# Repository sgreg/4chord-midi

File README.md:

# 4chord MIDI - The Four Chord USB MIDI Keyboard

What does it take to create a hit pop song?

Australia's former comedy group [The Axis of Awesome](https://en.wikipedia.org/wiki/The_Axis_of_Awesome) had the answer: [Four chords](https://www.youtube.com/watch?v=5pidokakU4I). Though not just any four chords, but the [I-V-vi-IV chord progression](https://en.wikipedia.org/wiki/I%E2%80%93V%E2%80%93vi%E2%80%93IV_progression) to be precise. This project implements a USB MIDI device for the purpose of playing this exact four-chord progression.

4chord MIDI is a regular USB MIDI controller, just like any other MIDI keyboard, except it has just four buttons, one for each chord in the I-V-vi-IV chord progression, playable in any key. But since simply playing chords is a bit limiting, it also features different playback modes such as triad arpeggios and chords mixed with arpeggios. Additionally, the tempo of each note progression is selectable from 30bpm to 240bpm. It's even shaped like a piano, to give the real feel of playing an actual musical instrument.

For additional information, check out [the 4chord MIDI project website](https://4chord.craplab.fi) and [its hackaday.io project page](https://hackaday.io/project/26078-4chord-midi).

4chord MIDI is fully open source and certified as such by the [Open Source Hardware Association (OSHWA)](https://www.oshwa.org/). The hardware is licensed under the [CERN Open Hardware License v.1.2](http://www.ohwr.org/projects/cernohl/wiki) and the software is released under the [GNU General Public License version 2](http://www.gnu.org/licenses/old-licenses/gpl-2.0.en.html).

<p align="center">

</p>

## Table of Contents
  * [Quick Start](#quick-start)
  * [Project Structure](#project-structure)
  * [Build it](#build-it)
  * [Flash it](#flash-it)
  * [Use it](#use-it)
  * [User Interface](#user-interface)
  * [Troubleshooting](#troubleshooting)

## Quick Start

If you're not interested in the details, here's the quickest way to build and flash a 4chord MIDI device. Note that the Makefile is set up to expect USBasp as programmer. If you're using a different programmer, check the [flashing section](#flash-it) for more details.

### Dependencies
Make sure you have the dependencies to build the bootloader and firmware installed on your system.

For Ubuntu, Debian, and the likes, this should be:
```
$ sudo apt install gcc-avr avr-libc avr-binutils avrdude make
```
For Fedora etc. it should be:
```
$ sudo dnf install avr-gcc avr-libc avr-binutils avrdude make
```
For Arch it should be ~~FUCKING OBVIOUS AND YOU'RE NOT WORTHY TO USE THIS GLORIOUS DISTRO IF YOU HAVE TO ASK A LAME QUESTION LIKE THIS~~ the same package names as for Fedora:
```
$ sudo pacman -S avr-gcc avr-libc avr-binutils avrdude make
```

Unfortunately, I don't have the answer for any other distribution, MacOS, or Windows, but essentially, it's just the regular AVR toolchain components (and `make`), so checking a general setup guide for the AVR toolchain on that system should get you there. Presumably it follows the same package names as mentioned so far.

### Cloning, Building, Flashing

Clone the repository and change into it:
```
$ git clone https://github.com/sgreg/4chord-midi.git
$ cd 4chord-midi/
```

Build the bootloader and firmware:
```
$ make
```

Make sure the ATmega's fuses are set up properly:
```
$ make fuses
```

Flash it to the device:
```
$ make program
```

That's it, your 4chord MIDI device should be ready to go, and once plugged in, recognized as as such. Check the [usage section](#use-it) for a quick overview of how to connect it to *FluidSynth* to get your first chords played.

If you *are* interested in more details, well here they come.

## Project Structure

* [`bootloader/`](bootloader/) the bootloader for comfortable firmware update flashing
* [`doc/`](doc/) some relevant documentation such as USB specifications
* [`firmware/`](firmware/) the main 4chord MIDI firmware code
* [`graphics/`](graphics/) raw [XBM](https://en.wikipedia.org/wiki/X_BitMap) files used within the GUI and intro animation
* [`hardware/`](hardware/) schematic and PCB design files
* [`sys/`](sys/) Linux system scripts (udev rules and setup scripts)
* [`tools/`](tools/) additional tools to convert graphics and dump fuse settings
* [`Makefile`](Makefile) main entry point to built it all
* [`common.mk`](common.mk) shared data related to building
* everything else: this README and git stuff

## Build it

From firmware point of view, there are three main parts to build here:
1. the raw XBM graphics converted to easily dump to the Nokia LCD (shipped pre-built)
1. the bootloader for future firmware updates via USB (optional but recommended)
1. the actual firmware

### Graphics
As the graphics parts come pre-built ([`intro.c`](firmware/intro.c)/[`intro.h`](firmware/intro.h) for the intro animation, [`gfx.c`](firmware/gfx.c)/[`gfx.h`](firmware/gfx.h) for all GUI related graphic elements), there's nothing to do, unless you want to change the [`graphics/`](graphics/) content by either adding new XBM files, or modifying the existing ones. In that case, once the graphics are modified, run:
```
$ make graphics
```
from the project's root path, which will delete all previously generated files and re-create them.

### Bootloader

You can build and flash the bootloader on its own without the main 4chord MIDI firmware. If this is your first time with the code, you might want to skip this option and go straight to the [Bootloader with Firmware](#bootloader-with-firmware) section for now.

But let's say you want to play around with just the bootloader and flash the application firmware through USB later, or make modifications to the bootloader itself. In that case, the bootloader can be built from the project's root directory via
```
$ make bootloader
```

or from within the `bootloader/device/` directory via `make` on its own.

This will create the bootloader's ELF and HEX file in the `bootloader/device/` directory, ready to be flashed to the device. Instructions on flashing [follow below](#flash-it).

**Note that this will build only the bootloader but not the firmware, so the device won't act as USB MIDI controller afterwards!**

Also note that once [flashed](#flash-it), the bootloader needs to be manually activated by pressing the *Select* button when powering the device up, otherwise it will fall through to the application code - which in this case won't exist. As a result, the device is stuck in a boot loop until the *Select* key is pressed. In other words, if the device seems dead after flashing the bootloader, just press the *Select* button to start up the actual bootloader.

### Firmware

As with the bootloader mentioned above, the firmware can be built and flashed on its own without adding the bootloader to it. This makes sense if you make any changes to the firmware code without touching the bootloader, but keep in mind that [flashing](#flash-it) the firmware on its own will leave out the bootloader, so future firmware updates via USB won't be possible (but you can always just re-flash the device with both components, so there's no harm done).

To build the firmware on its own from the project root directory, simply call

```
$ make firmware
```

To build it straight from within the `firmware/` directory, simply run `make` in there.

This will again create the ELF and HEX file inside the `firmware/` directory, and in addition, a BIN file. The HEX file is used for [flashing](#flash-it), while the BIN file is used in the firmware upgrade via USB using the bootloader.

### Bootloader with Firmware

To get the full package of bootloader and firmware, simply call
```
$ make
```
from within the project's root directory.

This will build both components separately, and the resulting ELF, HEX, and in case of the firmware, BIN file will be afterwards located in `bootloader/device/` and `firmware/` respectively.

You should now have either one of them built and ready to be flashed to the device.

## Flash it

If you're building your own device, you will require an AVR programmer to flash the initial bootloader and/or firmware to it. If you got a ready-made device, it will come with an initial bootloader and firmware already flashed on it, in which case you can either still use an AVR programmer to update it, or use the bootloader's built-in update functionality.

### Flashing with an AVR Programmer

The build system is set up to expect USBasp as programmer, so if you're using a different programmer, flashing is of course going to fail. To set up the build system for your programmer, check the [`common.mk`](common.mk) file for the following line:

```
AVRDUDE_PROGRAMMER_FLAGS = -c usbasp
```
and adjust it to your needs. If the programmer requires an additional port parameter, add the `-P <port>` accordingly.

Note that the device uses a 6-pin ISP connector, although some programmers - including a regular USBasp programmer - comes with a 10-pin connector. The 10-pin version has in the end just 4 additional, unused pins, which seems unnecessary, so the choice was to go for the 6-pin version here. The connectors are otherwise compatible, it just needs either an adapter or manual wiring.

To make sure the programmer is set up properly, connect it to the 4chord MIDI device and run
```
$ make check-programmer
```
from within the project's root directory. If both the programmer and device was detected, you should `SUCCESS` displayed in the end. Note that if you didn't connect the 4chord MIDI device, you might still see `FAILURE` even though the programmer is set up correctly. `avrdude`'s error message should hopefully give some hints which part went wrong then.

If everything is happily set up, connect the programmer to the device and get ready to flash.

Depending on the parts you [built earlier](#build-it), you can either flash the bootloader and firmware on its own, or nicely combined for the full experience.

For the latter, run the following command from the project's root directory:
```
$ make program
```
To flash only the bootloader, which won't include the firmware itself and therefore won't turn the device into an actual MIDI controller, run the command from within the bootloader directory:
```
$ cd bootloader/device/
$ make program
```
To flash only the firmware without the bootloader, flash it from the firmware's directory accordingly:
```
$ cd firmware/
$ make program
```

In case you included the firmware in your flashing, you're ready to [use it](#use-it). If you only flashed the bootloader and want to add the firmware through it, keep reading.

### Flashing via Bootloader

Whether the device runs *only* the bootloader, or the whole package, as long as there's a bootloader, you can use it to flash the actual 4chord MIDI firmware on it.

Flashing the firmware via bootloader involves two parts:
1. the activated bootloader on the device
2. the host-side flashing tool

To activate the bootloader, press the *Select* button while you power up the device, i.e. keep the *Select* button pressed when you plug in the USB cable to either your computer or the device itself. Instead of the 4chord MIDI startup animation and its user interface, you'll be greeted by the bootflash screen, telling you to feed it firmware.

The [host-side flashing tool](bootloader/host/) is a Python script using [PyUSB](https://github.com/pyusb/pyusb) to communicate with the bootloader - so make sure you have both Python 3 and the PyUSB module installed, whether through `pip` or your Linux distro's package manager.

With the device set up to receive new firmware, change into the host-side flashing tool's directory and run the script, giving the path of the new firmware's BIN file. If you built the firmware from its regular location, it will look like this:
```
$ cd bootloader/host/
$ ./bootflash.py ../../firmware/4chordmidi.bin
```

As you run the script, you will see some information and progress status displayed on the command line, and the device will show a progress bar on its screen. Once everything is done, you're ready to boot into the new firmware.

You can either just unplug the cable and plug it back in (making sure not to press the *Select* button this time), or press the *I* and *IV* playback button (i.e. the left-most and right-most white buttons).

## Use it

This section exclusive covers using the device under Linux, but since 4chord MIDI implements standard USB and MIDI specifications, other operating systems should treat it just like any other MIDI device. The general instructions of using MIDI devices on other operating systems should therefore apply also to 4chord MIDI.

### Plug it in

Connect 4chord MIDI to your computer and check if it got recognized. `dmesg` or the system log should show something like this:
```
[3038097.883853] usb 1-1.1.1: new low-speed USB device number 112 using ehci-pci
[3038099.140623] usb 1-1.1.1: New USB device found, idVendor=1209, idProduct=deaf
[3038099.140626] usb 1-1.1.1: New USB device strings: Mfr=1, Product=2, SerialNumber=0
[3038099.140627] usb 1-1.1.1: Product: 4chord MIDI
[3038099.140628] usb 1-1.1.1: Manufacturer: CrapLab
```

And thanks to [pid.codes](http://pid.codes/), `lsusb` should show something like this:
```
Bus 001 Device 112: ID 1209:deaf Generic CrapLab 4chord MIDI
```
Of course, the bus and device number will most certainly differ, but as long as the VID/PID pair (`1209:deaf`) is the same, it's all good.

### Simple playback with FluidSynth

As 4chord MIDI is just the controller in the MIDI chain, you will need a synthesizer to turn the playback into actual music. A cross-platform choice for this is for example the [FluidSynth software synthesizer](https://en.wikipedia.org/wiki/FluidSynth) in combination with its related sound font files.

FluidSynth can use different audio driver, including ALSA, PulseAudio, and [jack](https://en.wikipedia.org/wiki/JACK_Audio_Connection_Kit). To make life easy, let's use ALSA for this example.

#### Dependencies
Here's how to install ALSA utilities, FluidSynth with the sound fonts, and the resulting path of the sound font file we'll need afterwards.

Ubuntu / Debian / etc:
```
$ sudo apt install fluidsyinth fluid-soundfont-gm alsa-utils
/usr/share/sounds/sf2/FluidR3_GM.sf2
```
Note that the soundfont might also be named `fluidsynth-soundfont-gm` in older versions

Fedora etc:
```
$ sudo dnf install fluidsynth fluid-soundfont-gm alsa-utils
/usr/share/soundfonts/FluidR3_GM.sf2
```
Arch:
```
$ sudo pacman -S fluidsynth soundfont-fluid alsa-utils
/usr/share/soundfonts/FluidR3_GM.sf2
```

Again, for other distributions and operating systems, check the internet.

#### Running FluidSynth

Open up a terminal and start FluidSynth:

```
$ fluidsynth -a alsa -m alsa_seq /usr/share/soundfonts/FluidR3_GM.sf2
```

Make sure to use the correct sound font path according to your distro / operating system.

Once FluidSynth is started, and a 4chord MIDI device is connected to your computer, we need to connect the two using `aconnect` from the ALSA utils. Open up another terminal and check the input and output port IDs of the two parties involved.

```
$ aconnect -i
client 20: '4chord MIDI' [type=kernel]
    0 '4chord MIDI MIDI 1'

$ aconnect -o
client 129: 'FLUID Synth (32590)' [type=user]
    0 'Synth input port (32590:0)'
```

Your output probably shows more devices in each command, but those are the ones to look for. It tells us that 4chord MIDI is input port `20:0` and FluidSynth as MIDI output is port `129:0`. All that's left to do is connect the two:

```
$ aconnect 20:0 129:0
```

That's it. If you press any of the white playback buttons, you should hear a piano sound of the chords. Congratulations!

#### Changing instruments

If you want a change from the default Yamaha Grand Piano, go back to the terminal that runs FluidSynth and check the list of available instruments within its own command line. Since there's only one sound font file, its ID is simply `1`.
```
> inst 1
000-000 Yamaha Grand Piano
000-001 Bright Yamaha Grand
000-002 Electric Piano
...
000-025 Steel String Guitar
...
>
```

Changing the playback instrument for example to the Steel String Guitar (instrument id 25) for the default MIDI channel 0 is done via the `prog <chan> <instrument>` command:
```
> prog 0 25
```

You should now hear a guitar sound from the 4chord MIDI device.

### Automatic FluidSynth Setup

If you want to start FluidSynth automatically when you connect a 4chord MIDI device to you computer, you can do so on Linux with a udev rule. Check the [`sys/udev/`](sys/udev/) directory for further information on that.

## User Interface

If you got this far and everything worked as described, congratulations once again - and to both of us I guess, seeing that what I wrote actually worked out. If it didn't, well, there's a [troubleshooting section](#troubleshooting) still to come.

Now that the device is ready to be fully used, it's time give a quick introduction to its user interface.

### Display

The display consists of 4 components:
1. the menu bar on top, showing key, mode, tempo, and metre, underlining the one currently active
1. the playback setup information in form of key (C, C#, ..., Bb), tempo (30...240), metre (4/4, 3/4. 6/8), and playback mode (chord, arpeggios - shown in a simple form of musical notation)
1. the available chords for the currently selected key, highlighting the one that is currently played
1. a metronome if the playback mode is not just the simple chord playback

The menu buttons will control the content on the display.

### Menu Buttons
The three black buttons - `<`, `Select`, and `>` - serve as menu buttons and are used to control the key, mode, tempo, and metre:
* `Select` toggles between which part to control, i.e. key, mode, tempo, or metre
* `<` and `>` choose each part's value in an down/up and previous/next manner respectively

For example, if the *key* is the active component, and the active key is "C", `<` will change it to "Bb", and `>` will change it to "C#". Pressing `Select` twice will set the active component to `tempo`, and `<` will not decrease it, while `>` will increase it.

Both `<` and `>` have a long-press feature, meaning if keeping the button pressed, multiple press events are recognized, eventually speeding up.

For the time being, a long press on the `Select` button will save the current setup (key, mode, tempo, metre) as the device's default settings, so next time the device is powered on, it will recover those as its initial state.

### Playback buttons

The four playback buttons - `I`, `V`, `vi`, `IV` - are used to play each one of the four chords. That's basically it.

And yes, this section could most certainly use some visual aid.

## Troubleshooting

Obviously, everything I write and explain *works for me*&trade;, so it's difficult to anticipate difficulties others might have. Therefore the list of known problems is pretty limited at this point, but feel free to open an issue or contact me you come across some problems yourself.

#### Nothing happens when plugging in the device, and the display stays black
The flash might be either empty, or only the bootloader was flashed. Press the *Select* button and see if a bootflash screen comes up on the display. If yes, the application side wasn't flashed. If not, try re-flashing everything. See the [flashing section](#flash-it) either way.

#### Flashing firmware via bootloader fails with `usb.core.USBError: [Errno 13] Access denied (insufficient permissions)`
The device permissions are not set up for your user. You can either use `sudo`, or check the [bootloader/ directory](bootloader/) README about setting up a udev rule.

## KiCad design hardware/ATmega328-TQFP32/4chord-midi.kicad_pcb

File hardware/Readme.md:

## 4chord MIDI schematic and PCB layout files

**Note:** All content was designed using KiCad 4. Some files might not work with older versions of KiCad (actually, I haven't tried that). Schematics are additionally provided in PDF and PCB layouts in Gerber format.

Subdirectory content:

- Atmega328-TQFP32:
    - SMD version
    - 32pin TQFP ATmega328
    - Nokia 3310 LCD

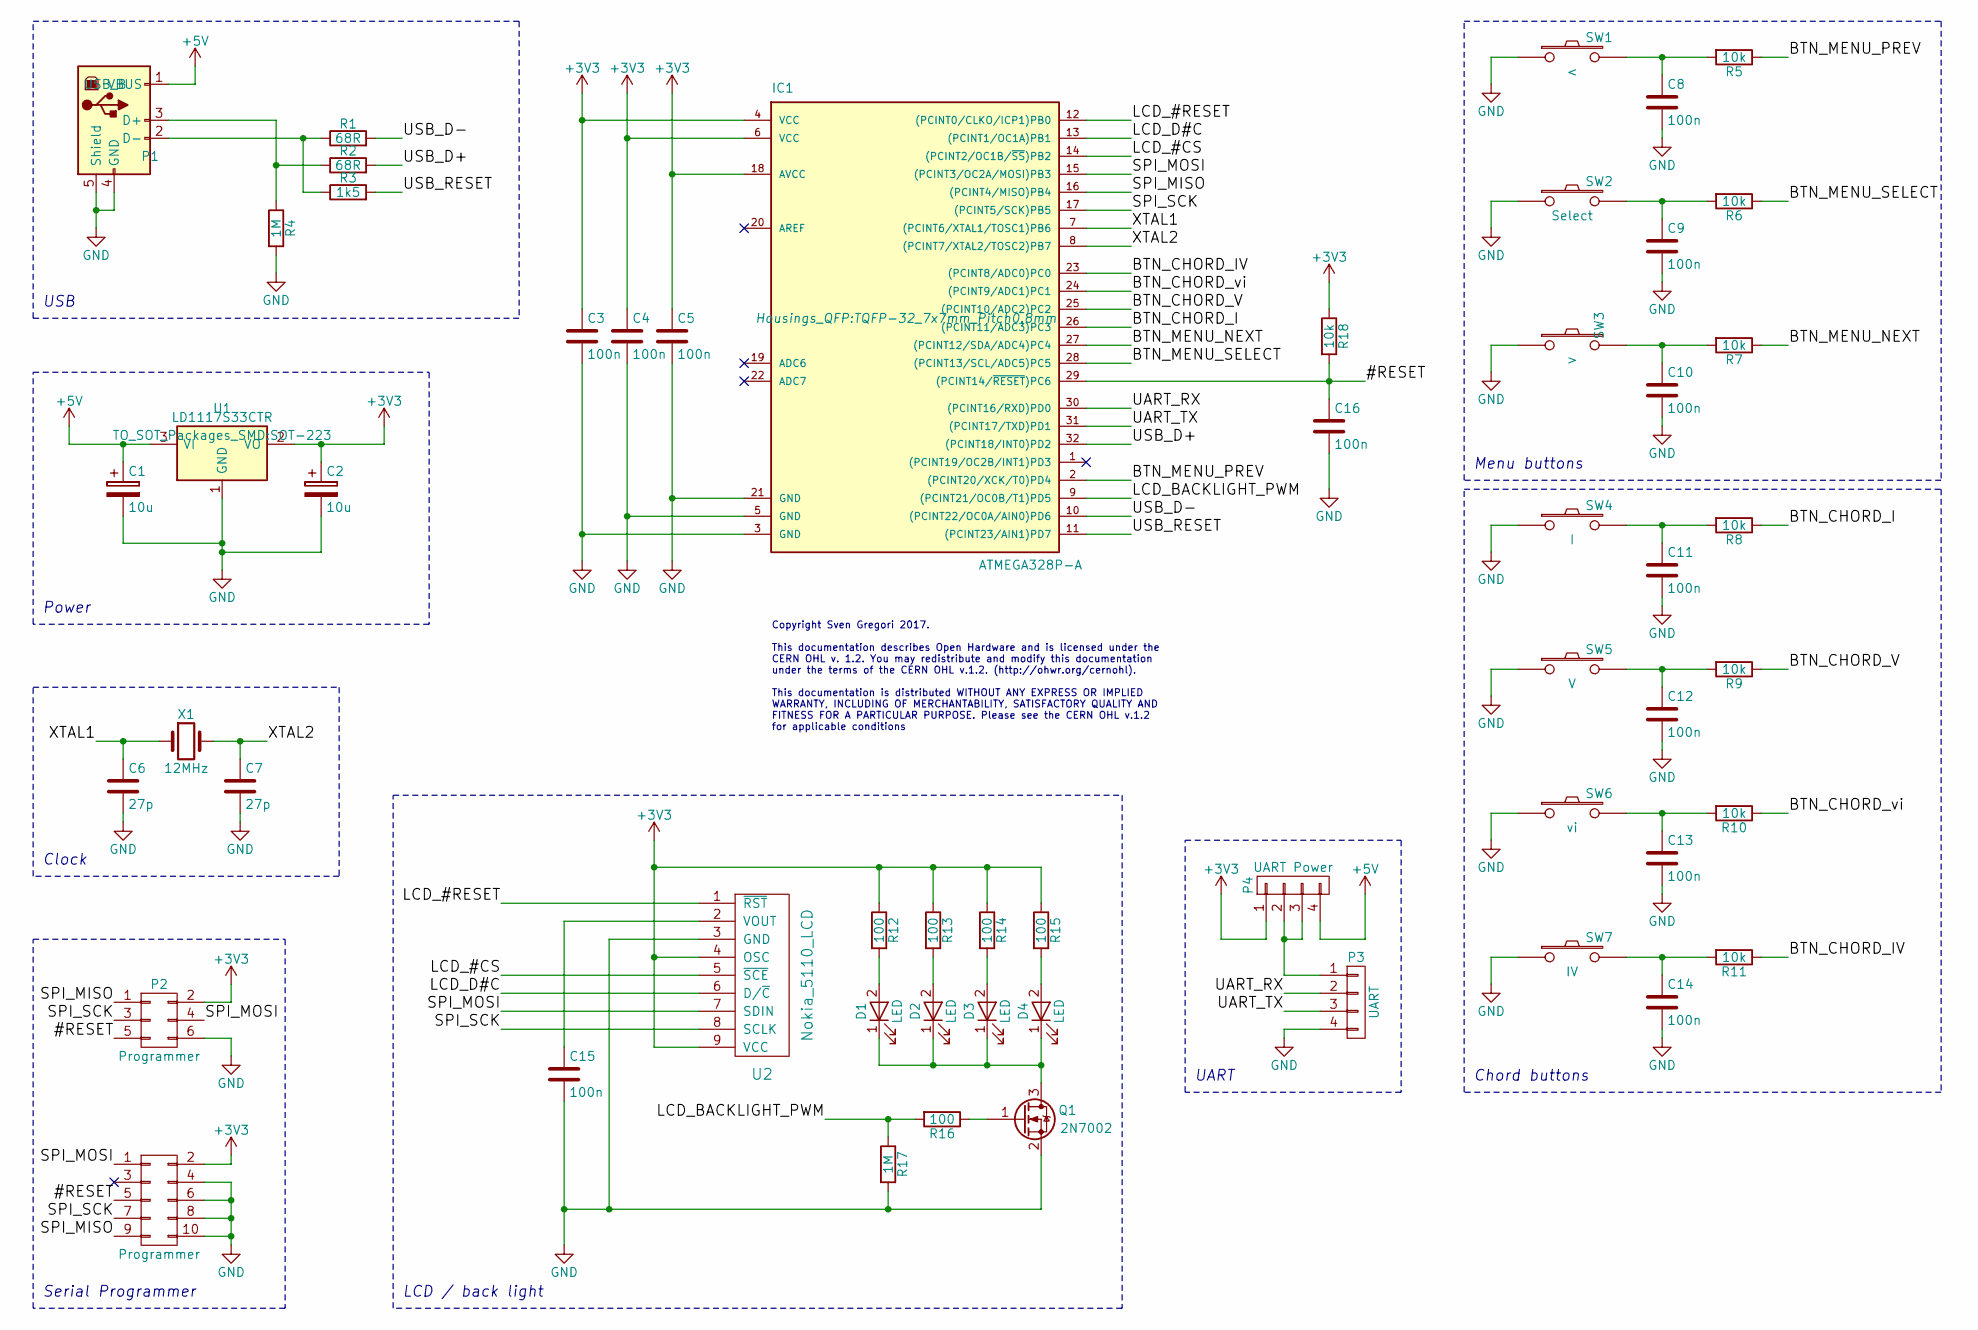
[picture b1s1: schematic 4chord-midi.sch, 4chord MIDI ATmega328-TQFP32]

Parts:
C1, C2: 10u; CP_Tantalum_Case-A_EIA-3216-18_Hand
C3, C4, C5, C8, C9, C10, C11, C12, C13, C14, C15, C16: 100n; C_0805_HandSoldering
C6, C7: 27p; C_0805_HandSoldering
D1, D2, D3, D4: LED; LED_0805
IC1: ATMEGA328P-A; TQFP-32_7x7mm_Pitch0.8mm
P1: USB_B; USB_Mini-B
P2: Programmer; IDC_Header_Straight_6pins
P3: UART; Pin_Header_Straight_1x04_Pitch2.54mm
P4: UART Power; Pin_Header_Straight_1x04_Pitch2.54mm
Q1: 2N7002; SOT-23
R1, R2: 68R; R_0805_HandSoldering
R3: 1k5; R_0805_HandSoldering
R4, R17: 1M; R_0805_HandSoldering
R5, R6, R7, R8, R9, R10, R11, R18: 10k; R_0805_HandSoldering
R12, R13, R14, R15, R16: 100; R_0805_HandSoldering
SW1: <; SW_SPST_EVPBF
SW2: Select; SW_SPST_EVPBF
SW3: >; SW_SPST_EVPBF
SW4: I; SW_SPST_EVPBF
SW5: V; SW_SPST_EVPBF
SW6: vi; SW_SPST_EVPBF
SW7: IV; SW_SPST_EVPBF
U1: LD1117S33CTR; SOT-223
U2: Nokia_5110_LCD; Nokia_5110-3310_LCD
X1: 12MHz; Crystal_SMD_HC49-SD

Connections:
+5V: C1.1, P1.1 (VBUS), P4.4, U1.3 (VI)
/BTN_CHORD_I: IC1.26 ((PCINT11/ADC3)PC3), R8.1
/BTN_CHORD_IV: IC1.23 ((PCINT8/ADC0)PC0), R11.1
/BTN_CHORD_V: IC1.25 ((PCINT10/ADC2)PC2), R9.1
/BTN_CHORD_vi: IC1.24 ((PCINT9/ADC1)PC1), R10.1
/BTN_MENU_NEXT: IC1.27 ((PCINT12/SDA/ADC4)PC4), R7.1
/BTN_MENU_PREV: IC1.2 ((PCINT20/XCK/T0)PD4), R5.1
/BTN_MENU_SELECT: IC1.28 ((PCINT13/SCL/ADC5)PC5), R6.1
/LCD_#CS: IC1.14 ((PCINT2/OC1B/~SS~)PB2), U2.5 (~SCE)
/LCD_#RESET: IC1.12 ((PCINT0/CLKO/ICP1)PB0), U2.1 (~RST)
/LCD_BACKLIGHT_PWM: IC1.9 ((PCINT21/OC0B/T1)PD5), R16.2, R17.1
/LCD_D#C: IC1.13 ((PCINT1/OC1A)PB1), U2.6 (D/~C)
/UART_RX: IC1.30 ((PCINT16/RXD)PD0), P3.2
/UART_TX: IC1.31 ((PCINT17/TXD)PD1), P3.3
/USB_D+: IC1.32 ((PCINT18/INT0)PD2), R2.2
/USB_D-: IC1.10 ((PCINT22/OC0A/AIN0)PD6), R1.2
/USB_RESET: IC1.11 ((PCINT23/AIN1)PD7), R3.2
/XTAL1: C6.1, IC1.7 ((PCINT6/XTAL1/TOSC1)PB6), X1.1
/XTAL2: C7.1, IC1.8 ((PCINT7/XTAL2/TOSC2)PB7), X1.2
unnamed: C8.1, R5.2, SW1.2
unnamed: C9.1, R6.2, SW2.2
unnamed: C10.1, R7.2, SW3.2
unnamed: C11.1, R8.2, SW4.2
unnamed: C12.1, R9.2, SW5.2
unnamed: C13.1, R10.2, SW6.2
unnamed: C14.1, R11.2, SW7.2
unnamed: C15.1, U2.2 (VOUT)
unnamed: D1.1 (K), D2.1 (K), D3.1 (K), D4.1 (K), Q1.3 (D)
unnamed: D1.2 (A), R12.2
unnamed: D2.2 (A), R13.2
unnamed: D3.2 (A), R14.2
unnamed: D4.2 (A), R15.2
unnamed: P1.2 (D-), R1.1, R3.1
unnamed: P1.3 (D+), R2.1, R4.1
unnamed: P3.1, P4.2, P4.3
unnamed: Q1.1 (G), R16.1

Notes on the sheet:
Copyright Sven Gregori 2017. This documentation describes Open Hardware and is licensed under the CERN OHL v. 1.2. You may redistribute and modify this documentation under the terms of the CERN OHL v.1.2. (http://ohwr.org/cernohl). This documentation is distributed WITHOUT ANY EXPRESS OR IMPLIED WA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
Clock
Serial Programmer
LCD / back light
Power
USB
UART
Menu buttons
Chord buttons

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
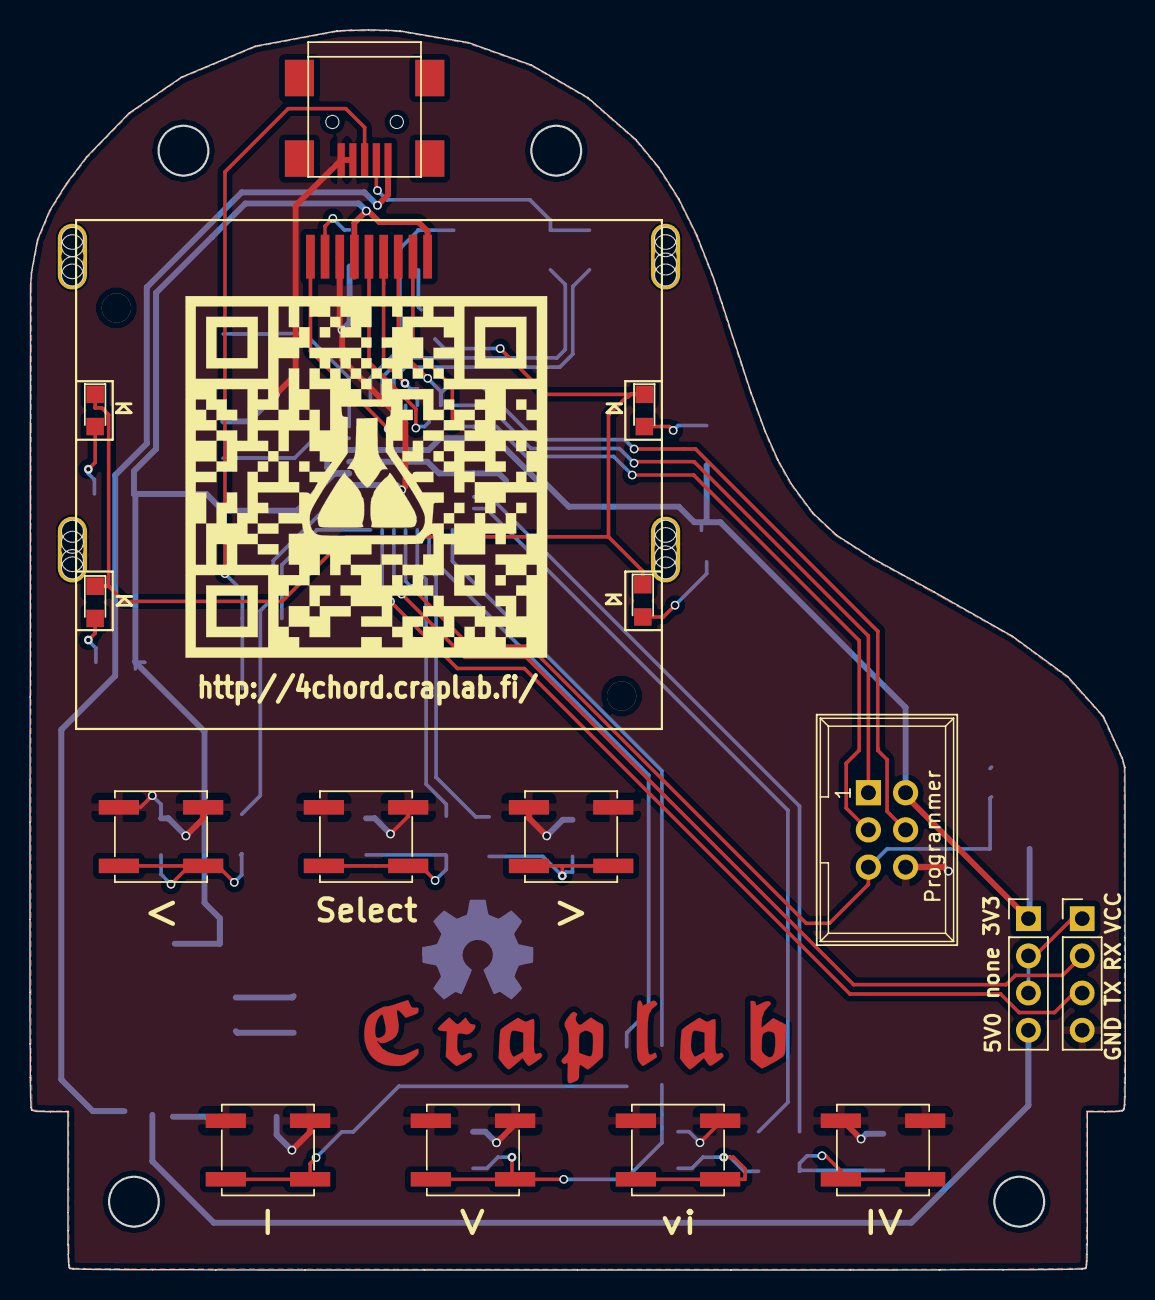
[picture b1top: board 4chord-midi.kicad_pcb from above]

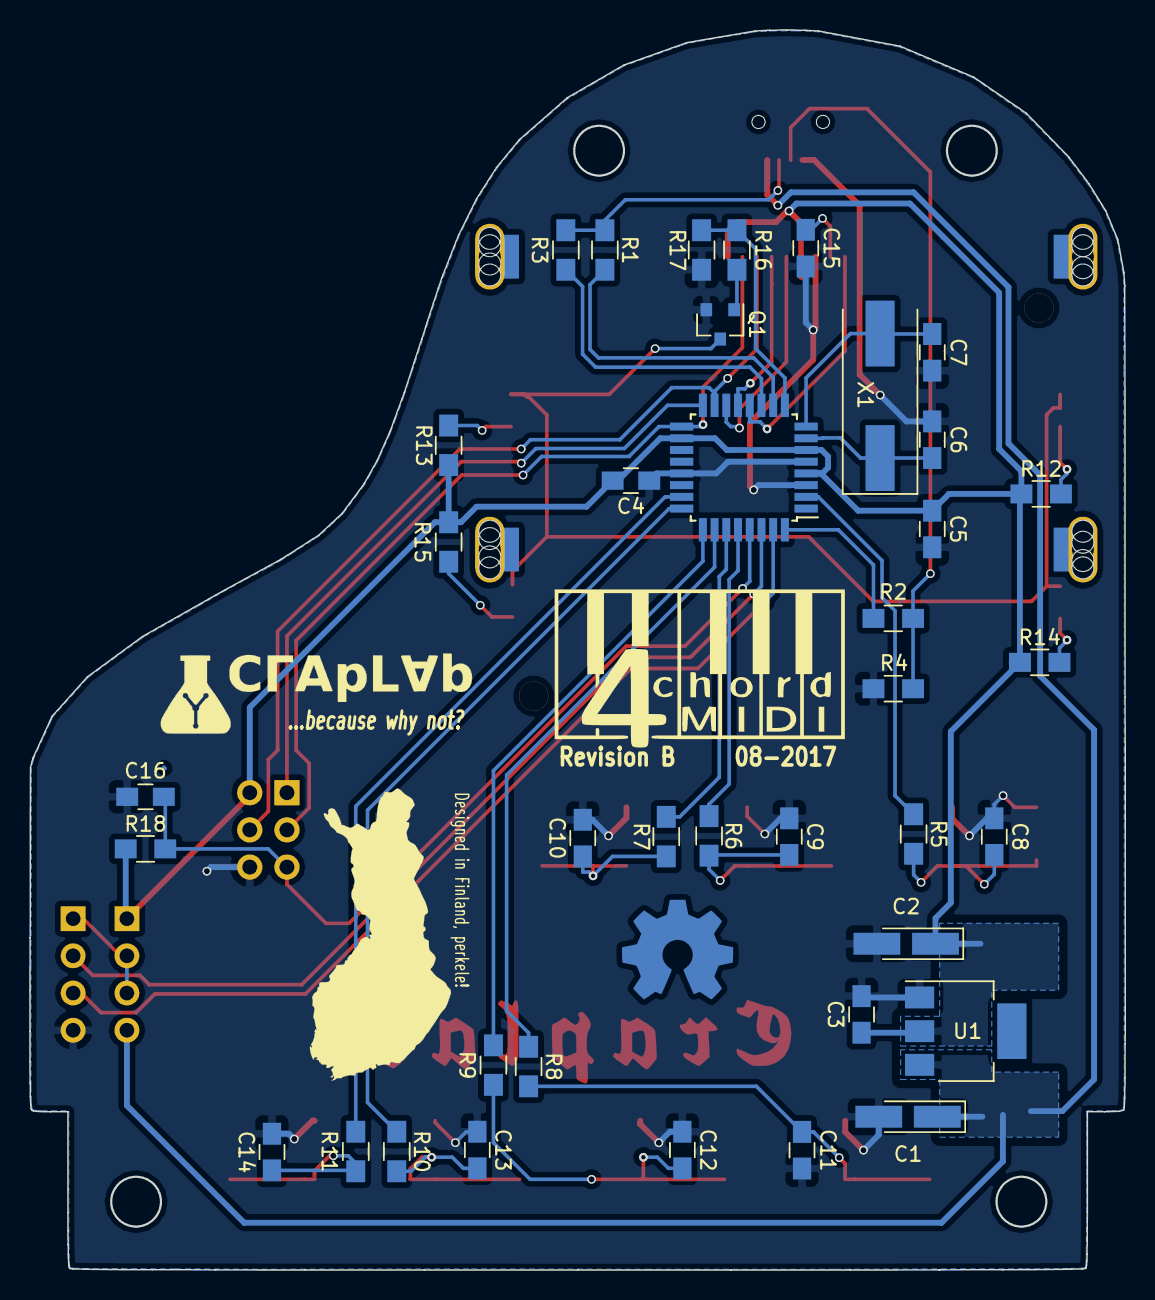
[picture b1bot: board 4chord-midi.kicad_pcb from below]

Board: 2 copper layers, 74.8 x 84.7 mm, 62 parts (43 on the bottom side), 42 nets.

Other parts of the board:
G1: LOGO; craplab-fraktur-Mask
G2: LOGO; craplab-fraktur-Cu
G3: LOGO; oshw-mask
G4: LOGO; oshw-cooper
G11: qr; projpage-QR-code-inv
G12: 4chordmidi; 4chord-midi
G22: craplab
G31: finland

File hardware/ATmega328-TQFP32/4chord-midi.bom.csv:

"Reference","Value","Datasheet","Footprint","Qty","DNP"
"C1,C2","10u","","Capacitors_Tantalum_SMD:CP_Tantalum_Case-A_EIA-3216-18_Hand","2",""
"C3,C4,C5,C8,C9,C10,C11,C12,C13,C14,C15,C16","100n","","Capacitors_SMD:C_0805_HandSoldering","12",""
"C6,C7","27p","","Capacitors_SMD:C_0805_HandSoldering","2",""
"D1,D2,D3,D4","LED","","LEDs:LED_0805","4",""
"IC1","ATMEGA328P-A","","Housings_QFP:TQFP-32_7x7mm_Pitch0.8mm","1",""
"P1","USB_B","","Connect:USB_Mini-B","1",""
"P2","Programmer","","Connect:IDC_Header_Straight_6pins","1",""
"P3","UART","","Pin_Headers:Pin_Header_Straight_1x04_Pitch2.54mm","1",""
"P4","UART Power","","Pin_Headers:Pin_Header_Straight_1x04_Pitch2.54mm","1",""
"Q1","2N7002","","TO_SOT_Packages_SMD:SOT-23","1",""
"R1,R2","68R","","Resistors_SMD:R_0805_HandSoldering","2",""
"R3","1k5","","Resistors_SMD:R_0805_HandSoldering","1",""
"R4,R17","1M","","Resistors_SMD:R_0805_HandSoldering","2",""
"R5,R6,R7,R8,R9,R10,R11,R18","10k","","Resistors_SMD:R_0805_HandSoldering","8",""
"R12,R13,R14,R15,R16","100","","Resistors_SMD:R_0805_HandSoldering","5",""
"SW1","<","","Buttons_Switches_SMD:SW_SPST_EVPBF","1",""
"SW2","Select","","Buttons_Switches_SMD:SW_SPST_EVPBF","1",""
"SW3",">","","Buttons_Switches_SMD:SW_SPST_EVPBF","1",""
"SW4","I","","Buttons_Switches_SMD:SW_SPST_EVPBF","1",""
"SW5","V","","Buttons_Switches_SMD:SW_SPST_EVPBF","1",""
"SW6","vi","","Buttons_Switches_SMD:SW_SPST_EVPBF","1",""
"SW7","IV","","Buttons_Switches_SMD:SW_SPST_EVPBF","1",""
"U1","LD1117S33CTR","","TO_SOT_Packages_SMD:SOT-223","1",""
"U2","Nokia_5110_LCD","","Nokia_5110-3310_LCD:Nokia_5110-3310_LCD","1",""
"X1","12MHz","","Crystals:Crystal_SMD_HC49-SD","1",""

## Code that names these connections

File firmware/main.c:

/*
 * 4chord MIDI - main
 *
 * Copyright (C) 2019 Sven Gregori <sven@craplab.fi>
 *
 * This program is free software: you can redistribute it and/or
 * modify it under the terms of the GNU General Public License
 * version 2 as published by the Free Software Foundation.
 *
 * This program is distributed in the hope that it will be useful,
 * but WITHOUT ANY WARRANTY; without even the implied warranty of
 * MERCHANTABILITY or FITNESS FOR A PARTICULAR PURPOSE. See the
 * GNU General Public License for more details.
 *
 * You should have received a copy of the GNU General Public License
 * along with this program. If not, see http://www.gnu.org/licenses/
 *
 *
 * ATmega328 pin layout (TQFP32)
 *
 *   1  PD3     (unused)
 *   2  PD4     I   Button menu prev
 *   3  GND     -
 *   4  VCC     -
 *   5  GND     -
 *   6  VCC     -
 *   7  PB6     -   XTAL1
 *   8  PB7     -   XTAL2
 *
 *   9  PD5     O   LCD back light
 *  10  PD6     I   USB D-
 *  11  PD7     O   USB Reset
 *  12  PB0     O   LCD /Reset
 *  13  PB1     O   LCD D/C
 *  14  PB2     O   LCD /CS
 *  15  PB3     O   LCD MOSI / SerProg MOSI
 *  16  PB4     I   SerProg MISO
 *
 *  17  PB5     O   LCD SCK / SerProg SCK
 *  18  AVCC    -
 *  19  ADC6    (unused)
 *  20  AREF    -
 *  21  GND     -
 *  22  ADC7    (unused)
 *  23  PC0     I   Button Chord IV
 *  24  PC1     I   Button Chord vi
 *
 *  25  PC2     I   Button Chord V
 *  26  PC3     I   Button Chord I
 *  27  PC4     I   Button Menu Select
 *  28  PC5     I   Button Menu Next
 *  29  PC6     -   /Reset
 *  30  PD0     I   UART RXD
 *  31  PD1     O   UART TXD
 *  32  PD2     I   USB D+
 *
 */
#include <stdint.h>
#include <avr/interrupt.h>
#include <avr/io.h>
#include <util/delay.h>
#include "buttons.h"
#include "cli.h"
#include "eeprom.h"
#include "lcd.h"
#include "menu.h"
#include "xbmlib.h"
#include "intro.h"
#include "gui.h"
#include "playback.h"
#include "spi.h"
#include "timer.h"
#include "uart.h"
#include "usbdrv/usbdrv.h"

/** number of steps to increase the PWM timer value during the intro */
#define INTRO_PWM_STEP_INCREASE 4

/** number of PWM timer increase steps per single intro frame */
#define INTRO_PWM_STEPS_PER_FRAME 5


int
main(void) {
    /* half the frame count of the intro animation, start USB at that point */
    const uint8_t frame_count_usb_threshold = intro_frames_count >> 1;
    /* PWM timer value for fading LCD back light during intro animation */
    uint8_t pwm_value;
    /* intro animation frame count */
    uint8_t frame;
    /* a happy little counter */
    uint8_t i;

    /* set PB0, PB1, PB2, PB3, PB4 as output, rest input */
    DDRB  = (1 << DDB0) | (1 << DDB1) | (1 << DDB2) | (1 << DDB3) | (1 << DDB5);
    /* set PB2 high, all other outputs low, enable pullups for all inputs */
    PORTB = ~((1 << PB0) | (1 << PB1) | (1 << PB3) | (1 << PB5));
    /* set port C all inputs */
    DDRC = 0x00;
    /* enable pullups for all inputs */
    PORTC = 0xff;
    /* set PD1 and PD5 as output, rest input. */
    DDRD  = (1 << DDD1) | (1 << DDD5);
    /* set outputs high, enable pullups for all inputs except V-USB ones */
    PORTD = ~((1 << PD2) | (1 << PD5) | (1 << PD6) | (1 << PD7)) & 0xff;

    uart_init(UART_BRATE_38400_12MHZ);
    uart_clear_screen();

    spi_init();
    lcd_rst_low();

    /* this should give enough delay for the LCD to reset */
    eeprom_init();
    cli_print();

    lcd_rst_high();
    lcd_init();

    /* set up LCD backlight timer and show the first intro animation frame */
    timer0_init_pwm();

    sei();

    /*
     * disconnect USB for a while to get (re-)enumeration ongoing
     * see also http://vusb.wikidot.com/driver-api
     */
    usbDeviceDisconnect();

    /*
     * show the intro animation and fade the back light up
     *  - linear PWM duty cycle increase every 10ms
     *  - show next frame after every 50ms
     * after half the animation frames, connect and initialize USB
     * every animation frame after that, start polling to keep the connection
     */
    for (frame = 0, pwm_value = 0; frame < intro_frames_count; frame++) {
        for (i = 0; i < INTRO_PWM_STEPS_PER_FRAME; i++) {
            timer0_set_pwm(pwm_value);
            pwm_value += INTRO_PWM_STEP_INCREASE;
            _delay_ms(10);
        }

        lcd_write_frame(&intro_frames[frame]);

        if (frame == frame_count_usb_threshold) {
            usbDeviceConnect();
            usbInit();
        } else if (frame > frame_count_usb_threshold) {
            usbPoll();
        }
    }

    /* wait some more to show the logo and slowly get the back light all up */
    while (pwm_value) {
        timer0_set_pwm(pwm_value++);
        usbPoll();
        _delay_ms(50);
    }

    /* map buttons to inputs */
    button_map_port(BUTTON_MENU_PREV,   &PIND, 4);
    button_map_port(BUTTON_MENU_SELECT, &PINC, 5);
    button_map_port(BUTTON_MENU_NEXT,   &PINC, 4);
    button_map_port(BUTTON_CHORD_I,     &PINC, 3);
    button_map_port(BUTTON_CHORD_V,     &PINC, 2);
    button_map_port(BUTTON_CHORD_vi,    &PINC, 1);
    button_map_port(BUTTON_CHORD_IV,    &PINC, 0);

    /* clear the display and show the menu */
    lcd_clear();
    menu_init();

    /* let the magic begin */
    while (1) {
        usbPoll();
        button_input_loop();
        playback_poll();
        menu_poll();
        cli_poll();
    }
}

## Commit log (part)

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2015-11-15 Initial commit, basic button handling, LCD handling and GUI
2015-11-16 added .gitignore
2015-11-19 issue-#3: integration of V-USB (and adding sources), setting up MIDI descriptors
2015-11-21 Add fuse dump tool to display AVR ATmega328p fuse byte settings
2015-11-21 Add global Makefile
2015-11-21 Added atmega328p_fuse_dump tool binary to gitignore
2015-11-22 issue-#3: re-arrange startup code to make USB work
2015-11-22 issue-#3: Added single-note MIDI playback on chord button press
2015-12-03 Added KiCad project for ATmega328-TQFP32
2015-12-03 issue-#1: Added schematic revision A for ATmega328-TQFP32
2015-12-03 Added KiCad backup and cache files
2015-12-03 issue-#1: fixed broken connection R4-GND
2015-12-03 issue-#1: Added test points and zero-Ohm links
2015-12-03 Fixed typos and other language issues in comments
2015-12-06 issue-#2: Added component footprints
2015-12-06 issue-#2: Added netlist
2015-12-06 issue-#2: Removed some grounding pins and changed footprints of remaining ones
2015-12-14 issue-#2: Added KiCad PCB layout
2015-12-14 issue-#2: Added Gerber files (KiCad naming scheme)
2015-12-14 Added comments on PCB artwork
2015-12-14 issue-#3: Added OSH Park compliant Gerber files as ZIP archive and script to create the ZIP archive from KiCad 4 naming scheme
2015-12-18 issue-#4: Moved menu handling from gui.c to new menu.c
2015-12-19 Added CERN OHL v.1.2 licensing documentation
2015-12-19 Added more information about graphics creation
2015-12-19 issue-#4: Added chord playback according to selected playback key
2015-12-19 issue-#5: Renamed chords.c to playback.c
2015-12-19 issue-#5: Added progressive playback handling for arpeggio and mixed chord/arpeggio modes
2015-12-20 issue-#5: Added UART command line interface handling for button emulation
2015-12-20 issue-#5: Removed unused case code
2015-12-20 issue-#5: Adjusted chord root notes
2015-12-20 issue-#5: Changed mode graphics to proper names
2015-12-22 Set version string to 1.0
2015-12-29 Fixed typo in fluidsynth command
2017-06-17 issue-#12: Initial version for Revision B hardware
    Changed crystal value from 16MHz to 12MHz to match speed spec for
    ATmega running at 3.3V. Changed LCD from Olimex Nokia 3310 with hard
    to find connector to Nokia 5110 breakout board style so it can be
    clipped directly into the PCB. Added LED based back light as well.
    Adjusted some pin assignments for ongoing PCB design
    Added BOM along the way.
2017-07-02 issue-#12: Completing Revision B schematic
    Further pin adjustments to get better PCB routing done. Changed
    programmer header from 10pin to 6pin for same reason.
2017-07-02 issue-#13: Initial Revision B PCB design
    Piano shaped PCB with debug interfaces: zero ohm links to all major
    power supplies, GND and UART voltage supply; GND test point; allows
    external (USB) UART connection (NOTE: do not equip R20 if USB UART
    controller is used)
2017-07-23 issue-#14: Adjust firmware to Revision B hardware changes
    Adjusted pin assignments according to Revision B hardware, changed clock
    frequency define from 16MHz to 12MHz (and re-arranged and neated up the
    Makefile along the way), enabled LCD backlight and changed LCD's bias
    system value for Nokia 5110 display.
    All okay in theory, waiting for PCB to build hardware and fully verify.
2017-08-09 issue-#13: Revised Revision B hardware
    Reworked schematic to separate to logical blocks, added reset circuit,
    fixed Q1 pin assignment and changed it from BJT to MOSFET component.
    Also added power supply choices for UART (5V, 3.3V and none) and a
    fourth rubber foot for better balance.
    Obviously same changes in the PCB design, also moved button silk screen
    bit more down for better readability. Fixed one sharp corner in the
2017-08-09 issue-#14: Changed USB VID/PID to 4chord MIDI's own
    Cheers to pid.codes for making this possible.
2017-08-19 issue-#15 Finalized Revision B hardware
    Final little touches here and there on the PCB design, mainly silk
    screen adjustments and moved the upper rubber feet.
    Alos, fucked up 00f85adde54214f45f219a16524527a8af92649b which should
    have been linked to issue-#15 as well. Oh well..
2017-08-19 Update README information for 1.1-B release
2017-08-26 Added udev rule example
    Simple udev rule example to automatically start fluidsynth and set up
    the MIDI connection to it whenever a 4chord MIDI device is plugged in,
    and clean it up again when the device is unplugged.
2017-09-12 Add schematic cache lib to repository
    Otherwise it's just fucked up anyway since KiCad generates default
    netlist now to reference the cache lib instead of the builtin
    components. Probably best this way with changes happening now and then
    in the builtin ones. Which I fixed here too, since someone had the grand
    idea to change the USB-B component's pin arrangement to 1-3-2-4-5 and
    swap D+ and D- order.
2017-10-19 issue-#17: Initial bootloader implementation
    Added device side bootloader implementation and host side Python script
    as flashing tool. Heavy restructuring of the Makefiles along the way to
    keep most of the overlapping parts in a common place.
2017-10-20 issue-#18: Changed playback handling to 1/8 notes
    Keeping same BPM values at 4/4 metre, the playback is now doubled, or
    well, the note interval halved. Playback modes got adjusted accordingly
2017-10-20 issue-#17: Adjusted USB config for PID and name
2017-10-20 issue-#17: Improved bootloader flash tool
    Cleaned up the proof of concept Python script to flash a new firmware
    through the bootloader. Simple output as default, detailed per-page
    output with additional verbose mode
2017-10-27 issue-#21: Added long press for menu buttons
    Got tired of single button press, especially when changing the tempo, so
    now there is long button press support for the menu buttons.
    For the "<" and ">" menu button, it keeps executing the prev and next
    functions. First with a 500ms delay for the first three iterations, then
    it speeds up to 100ms.
    For the "Select" menu button, long press will wait 1.5s and for now only
2017-10-28 issue-#19: Added chord list to LCD w/ highlight
    Each key's four chord's are now displayed on the LCD for easier
    visualization of what's actually available in each key. This should make
    it easier to play songs by chord - and also to find out whether a song
    is a 4chord song or not.
    It felt like a good idea to create a "font" for this instead of using
    individual graphics. Using quotes cause it doesn't really make any real
2017-10-28 issue-#20: Added metre playback and display support
    General support for metre concept added, and included new 3/4 and 6/8
    playback next to the regular 4/4 one. Well, at this current point, since
    all playback is based on 1/8 notes, the there is no difference between
    3/4 and 6/8 apart from LCD content.
    Added a font for this as well, could use some improvements still if
    something like 12/8 metre should be supported (there's only one digit
2018-05-07 issue-#25: Basic EEPROM support added to build system
    Added Makefile rules to create and flash EEPROM data from the ELF file,
    and changed fuse bits to preserve EEPROM during chip erase.
2018-05-07 issue-#25: Initial EEPROM data handling added
    Dummy EEPROM data defined and files are added to Makefile
2018-05-07 issue-#25: Playback init values are read from EEPROM
    Init values for playback chord/mode/metre/tempo are now stored on the
    EEPROM and menu initialization is based on those values.
    Long press on the Select key will store the current playback values as
    new init values to the EEPROM (still to be replaced by a general menu
    later on)
2018-12-23 issue-#28: Replaced graphics generation script with xbmtool
    XBM graphics are now converted using xbmtool.sh instead of the old
    create_graphics.sh script.
    Graphics generation support now both full frame / as-is data and diff
    frame based animations that modify only the values that changed to the
    previous animation frame.
    Also, input graphics don't need to be rotated and flipped anymore, but
2018-12-23 issue-#28: Arranged XBM graphics for new conversion script
    XBM files are now used as-is, no more rotating and flipping, the grahpic
    generation itself will take care of that.
    Also adding XBM files for the startup animation, and separating them
    from the regular UI graphics.
2019-02-16 Some random, minor cleanup and fixes
    - xbmtool doesn't abort `make` anymore if files aren't overwritten
    - udev install script didn't fully obey overwrite-existing-file choice,
    now it does and also outputs a tad more information
    - added some more information and debug output to fluidsynth script
    - added also some information about known issue with that script
    - cleaned up intro animation / light fading / USB init handling
2019-11-19 Bootflash script uses finally Python 3
    Dumped a bunch of parantheses around the prints.
    Also changed everything about the output in general, now with ASCII art!
2019-11-20 Refactored bootloader commands and added EEPROM support
    Changed random command values into slightly differently random values,
    renamed names and states along the way to make it more clear they're
    about firmware update. Added support to read and write EEPROM data for
    future use.
2020-06-13 Added Makefile rule to check programmer state
    To quickly check that the programmer is set up correctly and the ATmega
    is recognized, new Makefile rule is added.
    Programmer settings for avrdude was extracted into an own Makefile
    variable for easier adjustments to other programmers.
    Also made a global accessible fuse burning rule
2020-06-13 issue-#24: Updated and extended project's main README
    Add sections about building, flashing, and using the device
2020-06-13 issue-#24: Updated graphics and hardware README
2020-06-13 Added bootloader version string verification to bootflash
    Just in case, additional check is added to make sure the connected
    device identifies itself as valid 4chord MIDI bootloader device.
    Also, reading ASCII tables is hard, so the HELLO command values were
    messed up.
2020-06-13 issue-#24: Added bootloader README
2020-07-10 Fixed file headers for consistency
    It's now everywhere "4chord MIDI", in some places the "MIDI" wasn't
    capitalized. Seriously important work done here, I tell you.
2020-07-10 Added OSHWA certification mark
    Oh, hi Mark!
2020-07-10 Updated contact information
2020-07-10 Added short delay in bootloader UART output
    If the bootloader doesn't get activated but jumps straight to the
    application code, the UART might not finish its output in time and
    causes some garbage output. Things gotta look pretty, eh?
2020-07-10 Remove assembly listing files during make clean
    Used to be removed during `make distclean`, but kinda makes no sense as
    the .lst listing files belong to the .o files that are cleaned during
    `make clean` anyway.
2020-07-23 Added doc/ directory with local copies of relevant docs and specs
    Since the links to specifications were broken, I figured it's maybe best
    to just add a local copy just in case. While those links probably won't
    ever fully disappear, it's still annoying to end up with a 404 and
    having to search for the new location. So now they're also in the repo.
2020-08-21 Lowered PWM timer prescaler / increased PWM timer speed
    At F_CPU/256 prescaler, there's some subtle flickering noticable in some
    situations, especially when the entire display is filled. Might not be
    all too relevant in real world scenarios, but at F_CPU/64 prescaler, the
    flickering is gone, so, tadaa.
2020-08-21 Added EEPROM data versioning and update process
    If the EEPROM data structure changes in a way that is not backwards
    compatible, for example a new value is added that the firmware expects
    to be set to a certain range (like the LCD init values in the previous
    commit), the EEPROM version can now be increased, and an update check
    function can handle all the necessary steps to ensure all goes well.
2025-01-04 Tweak kitspace.org description
    Set additional information and add a CSV BOM
